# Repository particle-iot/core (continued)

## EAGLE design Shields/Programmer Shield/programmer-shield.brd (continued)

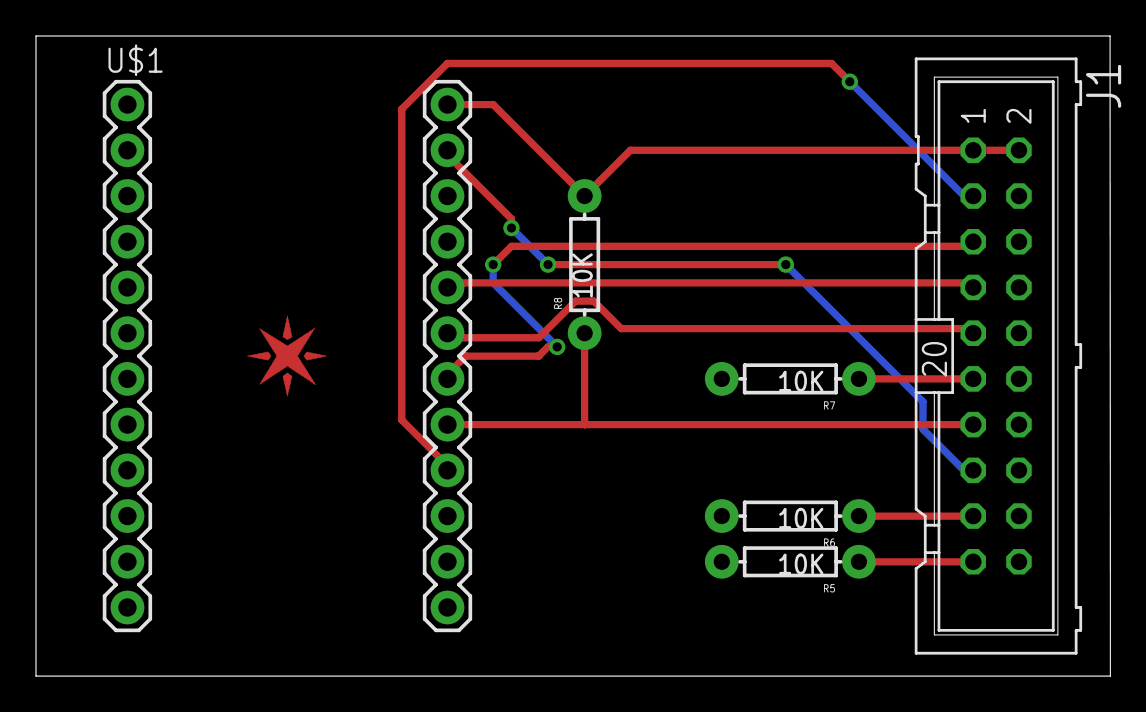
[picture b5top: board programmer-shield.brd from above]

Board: 2 copper layers, 59.7 x 35.6 mm, 7 parts (0 on the bottom side), 11 nets.

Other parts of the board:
E$1: SPARK_LOGO_PLUS_PLANE

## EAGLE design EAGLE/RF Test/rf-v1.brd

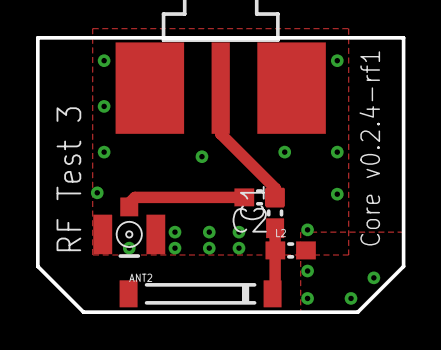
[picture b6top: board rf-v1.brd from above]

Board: 4 copper layers, 20.3 x 15.2 mm, 6 parts (0 on the bottom side), 4 nets.

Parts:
ANT2: AT8010
C1: 2.2pF; C0603
C2: 10pF; C0603
L2: 2.2nH; 0603
X1: SMA-142-0701-881/886; ANDYW-GENERIC-END-LAUNCH
X3: IPEX-20279-001E

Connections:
GND: L2.2, X1.G@1, X1.G@2, X1.G@3, X1.G@4, X3.2@1, X3.2@2
unnamed: ANT2.SIG, C1.1, L2.1
unnamed: C2.2, X3.1
unnamed: C1.2, C2.1

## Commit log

2013-03-24 First commit; complete board and schematic, untested
2013-03-25 Cleaned up fie structure
2013-03-25 Deleted moved files
2013-03-25 Integrated Satish's feedback
2013-03-25 Included Excel temp files in gitignore
2013-03-25 Updated with Andy's feedback
2013-03-25 Added CC3000-WG1300 datasheet
2013-03-26 Tweaked board to remove 90 degree angles
2013-03-26 Re-zipped gerber files
2013-03-26 Added programmer shield
2013-03-28 Added Bill of Materials
2013-03-28 Added part numbers for all parts
2013-03-30 Updated TODO with Satish's feedback
2013-03-31 WIP: Board and schematic are not matched
2013-03-31 Fixed re-numbering error by pulling in old board/schematic from 131d9d4
2013-03-31 Added datasheets
2013-04-01 Made all board revisions. Time for production
2013-04-02 Created gerber files for Core v0.0.6 and re-designed programmer shield
2013-04-02 Re-numbered components
2013-04-02 Updated bill of materials to v0.0.6
2013-04-02 Cleaned up schematic
2013-04-02 Cleaned up assembly sheet
2013-04-02 Created PDFs
2013-04-02 Added version numbers to finalized files
2013-04-03 Added changes for the next revision to the README
2013-04-03 Updated TODOs
2013-04-05 Updated EAGLE files with new WIFI_EN and WIFI_INT pins and better grounding
2013-04-05 Re-created gerber files
2013-04-05 Created drawings for v0.0.7
2013-04-05 Added Core Debug
2013-04-05 Deleted programmer shield (moved to Shields repo)
2013-04-08 Finished Core Debug v0.0.8
2013-04-08 Fixed MOSI/MISO error in Core
2013-04-08 Updated all output files for v0.0.8
2013-04-08 Added drill file to Core Debug Gerber
2013-04-10 Updated BOM and Debug board to prep for assembly
2013-04-15 Added Core SW pin mapping (from Spark-Wiring)
2013-04-18 Added prices to BoM
2013-05-02 Better USB, improved power layout, got rid of resistor near antenna
2013-05-02 Renumbered parts
2013-05-02 Re-ran gerber files
2013-05-10 Updated assembly sheets to v0.1.0
2013-05-16 Finished v0.1.0
2013-05-17 Initial commit, v0.1.0
2013-06-27 Updated assembly sheets to Letter size
2013-06-27 WIP for Issue #5, #7, #8, #9
2013-06-27 Added Spark Eagle Libraries and Updated .gitignore
2013-06-27 Moved crystals and capacitors away from RF area
2013-06-28 Footprints created for new parts
2013-06-28 Schematic completed as per latest issues list (Ready for review)
2013-06-28 Updated Footprints
2013-06-28 Updated schematic after initial review
2013-06-28 Laid out RF area, tweaked SPI flash area, placed buttons and LED
2013-06-28 RF tweaks based on @andyw-lala's feedback
2013-06-30 moved everything up and right 0.2 inches
2013-06-30 moved everything up and right by 0.2 inches
2013-06-30 Proposed RF layout.
    Added C12 and overlay common pad with C16.
    Added top ground plane - extended back under CC3000
    Moved Antenna closer to centre line of module.
2013-07-01 First pass at RF test board to evaluate quality and performance of RF component placement.
    To be connected directly to VNA for S11 (and S12 in the case of u.FL connector.)
    Can also be used with signnal generator to estimate antenna radiation pattern.
2013-07-01 Minor twak of SMA position. Remove thermals on bottom layer.
2013-07-01 Updated Spark Eagle Library
2013-07-01 Updated Schematic - Added Tantalum Cap for VDDA and Rearranged RGB Wiring
2013-07-01 Updated PCB Layout Component Placement
2013-07-01 Partial completed routing for end of the day
2013-07-02 Updated Datasheets
2013-07-02 Added new Tactile Switch Footprint to Library
2013-07-02 Tactile switch replaced in Schematic and Layout
2013-07-02 Components Locked and PCB Manual Routing 90% completed
2013-07-03 Renumbered components
2013-07-03 Added new BoM file
2013-07-03 Produced Gerber files for RF Test board
2013-07-03 Replaced C16 - Tantalum 0603 with Tantalum 1206
2013-07-03 Rearranged placement and routing of Crystal and SPI Flash area
2013-07-03 Finished Schematic and PCB Layout
2013-07-03 Minor tweaks to board
2013-07-04 Created Gerber files for v0.2
2013-07-04 Deleted Gerber files for v0.1
2013-07-07 Removed thermals on 3V3 & gnd pours. Added to and bottom layer gnd polygons around LDO. Tweaked via spacing slightly Moved D0 silk screen to match A0. Ran DRC and approved all clearance issues surrou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
2013-07-07 Moeverd top layer ground pours. Added additional gnd connection for user button to avoid isolated pad.
2013-07-07 Additional ground pour on bottom layer at south end of board.
2013-07-08 Added supplementary files for v0.2
2013-07-08 Renamed BoM file
2013-07-11 Created BoM for Core v0.2.1
2013-07-11 Added datasheets from manufacturer
2013-07-12 Integrated Will/Peter feedback
2013-07-12 Added fab note to BoM file; added DFM report
2013-07-12 Added drawing for RF circuit
2013-07-12 Added fab note and data sheets for antenna and USB connector
2013-07-16 Updated BoM
2013-07-17 Updated Crystal Section
2013-07-17 Updated USB Section
2013-07-17 Added new USB connector footprint to Spark Library
2013-07-17 Added a modified version of the new USB connector with slot holes
2013-07-17 Issue#22 modified and added the 1x12 pin header with smaller pads and holes to the spark library. Also modified the Core PCB with the updated header file issue#22 closed
2013-07-18 Added the new slotted hole USB connector as a Device Variant
2013-07-18 Updated the PCB Layout with the new slotted hole USB connector
2013-07-18 Removed 2/5 vias from REG pad and shifted the GND via away from CC3000 pad
2013-07-18 Added a GND copper pour on the bottom layer around the Regulator pad
2013-07-18 Added silkscreen to all 0603 parts
2013-07-18 Added CC3000 Pin 1 mark on PCB top silkscreen layer
2013-07-18 Updated RGB Led silkscreen
2013-07-18 Updated BOM and Datasheets
    Updated the core-bom-v021 based on actual parts ordered for production.
    Uploaded named PDF datasheets for every component with exception given
    to the RF capacitors that are still out for quotation and ordering.
2013-07-18 DRC Error checked, fault fixed and approved
2013-07-18 Shifted decoupling caps a bit away from the STM32
2013-07-18 Moved vias away from GND pads just a tad
2013-07-18 Updated all supplementary files
2013-07-21 Second revision of the RF Test board.
    Changes:
    1. 50Ohm trace width tweaked to 23mil (not so important since we will specify controlled impedance.)
    2. SMA footprint changed to accomodate 0.25" SMA connectors and present less of an impedance bump
    3. vias moved out of u.FL pads
    4. L1 silkscreen removed
2013-07-23 Updated BoM
    Updated the BOM to include Johanson RF passives.
2013-07-23 RF-Test-2 Gerbers
    Changed traces to 25mil, generated RF-Test-2 gerbers.
2013-07-24 Updated BOM
    Reverted back to 1/10W resistors, updated 3 ceramic capacitors with
    approved substitutes based on lead time and availability.
2013-07-24 Further BoM Corrections
    Updated 22Ohm P/N and last edited date
2013-07-30 Removed vias in voltage regulator pad, resolved Issue #34
2013-07-30 Moved vias out from under the u.FL connector
2013-08-01 Updated Core BOM and Stencils
2013-08-01 Fixed power plane
2013-08-01 Updated gerbers
2013-08-03 Updated BOM
    Updated all capacitors and resistors to reflect components purchase.
2013-08-07 undo PCB move
2013-08-08 merging branch to undo previous PCB move
2013-08-08 added diode, maintained changed RGB LED footprint, moved the PCB
2013-08-08 Via tweak to pass DRC
2013-08-08 Moved silkscreen on headers to bottom layer
2013-08-08 Created pi network
2013-08-08 0402 components
2013-08-09 Clean RF circuit with 0603
2013-08-09 Fixed up BoM
2013-08-09 Added gerbers
2013-08-09 Recreated drawings
2013-08-09 added oshw logo, changed sprak core footprint and changed power jack footprint
2013-08-09 deleted ghost files
2013-08-11 Design with counterpoise (series then parallel)
2013-08-11 Design with counterpoise (parallel then series)
2013-08-12 Additional proposed RF layout for review and discussion
2013-08-12 RF Test board updated to match. A0 silk screen moved on core.
2013-08-12 Reduce stripline length, shorten test board.
2013-08-12 Added counterpoise to GND plane, extended to mitred edge
2013-08-13 added the buffer on the MISO line of the CC3000
2013-08-13 Fixed DRC errors and Updated PCB routing and Power plane polygons
2013-08-13 Improved power plane
2013-08-13 Minor tweaks and cleanup
2013-08-13 More GNDing
2013-08-13 Shifted compoennts to provide perpendicular counterpoise
2013-08-13 Introduced tweaks from 'rf' branch
2013-08-14 Created gerbers, zip files, and updated BoM
2013-08-14 Moved LED away from under silkscreen
2013-08-14 Fixed assembly sheet
2013-08-14 Re-created zips and gerbers
2013-08-14 Re-created drawings
2013-08-14 Tweaked schematic and board layout for alternate matching components (parallel then series)
2013-08-14 Further layout tweaks
2013-08-14 Created gerbers and zips for rf-v2
2013-08-14 Quick schematic and layout for rf-v3
2013-08-14 Clean up design
2013-08-14 Created gerbers and zips
2013-08-14 Added RF test boards and their gerbers
2013-08-15 changed the net from WIFI_EN to WIFI_CS on the buffer chip
2013-08-15 Approved DRC warnings
2013-08-15 GERBERS AND ZIPSgit statusstatus
2013-08-15 Approved ERC warnings
2013-08-16 Rework RF matching to use 0402 components instead of 0603. Note that I couldn't find a trustworthy 0402 inductor footprint, so I used a 0402 capacitor instead - doesn't matter for the layout. The sma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
2013-08-25 Added Core BOM v025
    Updated v024 to v025
2013-09-03 Updated BOMs
    Worked with AQS to settle part identifiers
2013-09-04 Removed series element and included matching circuit
2013-09-04 More BOM Updates
2013-09-04 Cleaner, prettier RF design
2013-09-04 Fixed library part for RF capacitor
2013-09-06 updated the ufl footprint and changed the net from wifi_en to wifi_cs
2013-09-06 Cleaned up board and approved erc/drc errors
2013-09-06 Brought in Will's latest BOM file
2013-09-06 Deleted old BOM
2013-09-06 Updated BoM to v1
2013-09-06 Updated datasheets, drawings, and zips to v1
2013-09-06 Updated gerbers to v1
2013-09-07 Added old ECO Changes
    Inserted old ECO changes from previous BOMs
2013-09-13 increased the copper clearance around the two mounting holes on the USB connector
2013-09-17 changed labels and updated diode footprint
2013-09-19 added keepout on gnd layer around the oval pads of the USB connector
2013-09-24 added anular rings aroung the USB oval pads on 3V3 and GND layers
2013-10-05 Updated BOMs
    Updated BOMs with AQS part numbers recent as of 130926
2013-10-06 Updated BOM
    Updated BOM as of 092613
2013-10-28 Added 3528 RGB LED datasheet
2013-10-29 Minor BOM tweaks
    Minor BOM tweaks updated current as of 10/6
2013-10-29 More BOM tweaks
2013-11-19 added license file
2013-11-19 added license info within the design files
2014-03-04 Updated Mechanical Drawing
    Updated the mechanical drawing to reflect changes that were made to the
    pin names.
2014-07-09 Added in LDO Reg datasheet
2015-03-07 Updated to Spark
2016-05-05 Update license to CC-BY-SA 4.0
    Particle hardware files are licensed under Creative Commons Attribution Share-Alike
